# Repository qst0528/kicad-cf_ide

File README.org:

* CompactFlash cards and DMA/UDMA support in True IDE (tm) mode
http://support.fccps.cz/download/adv/frr/cf.html

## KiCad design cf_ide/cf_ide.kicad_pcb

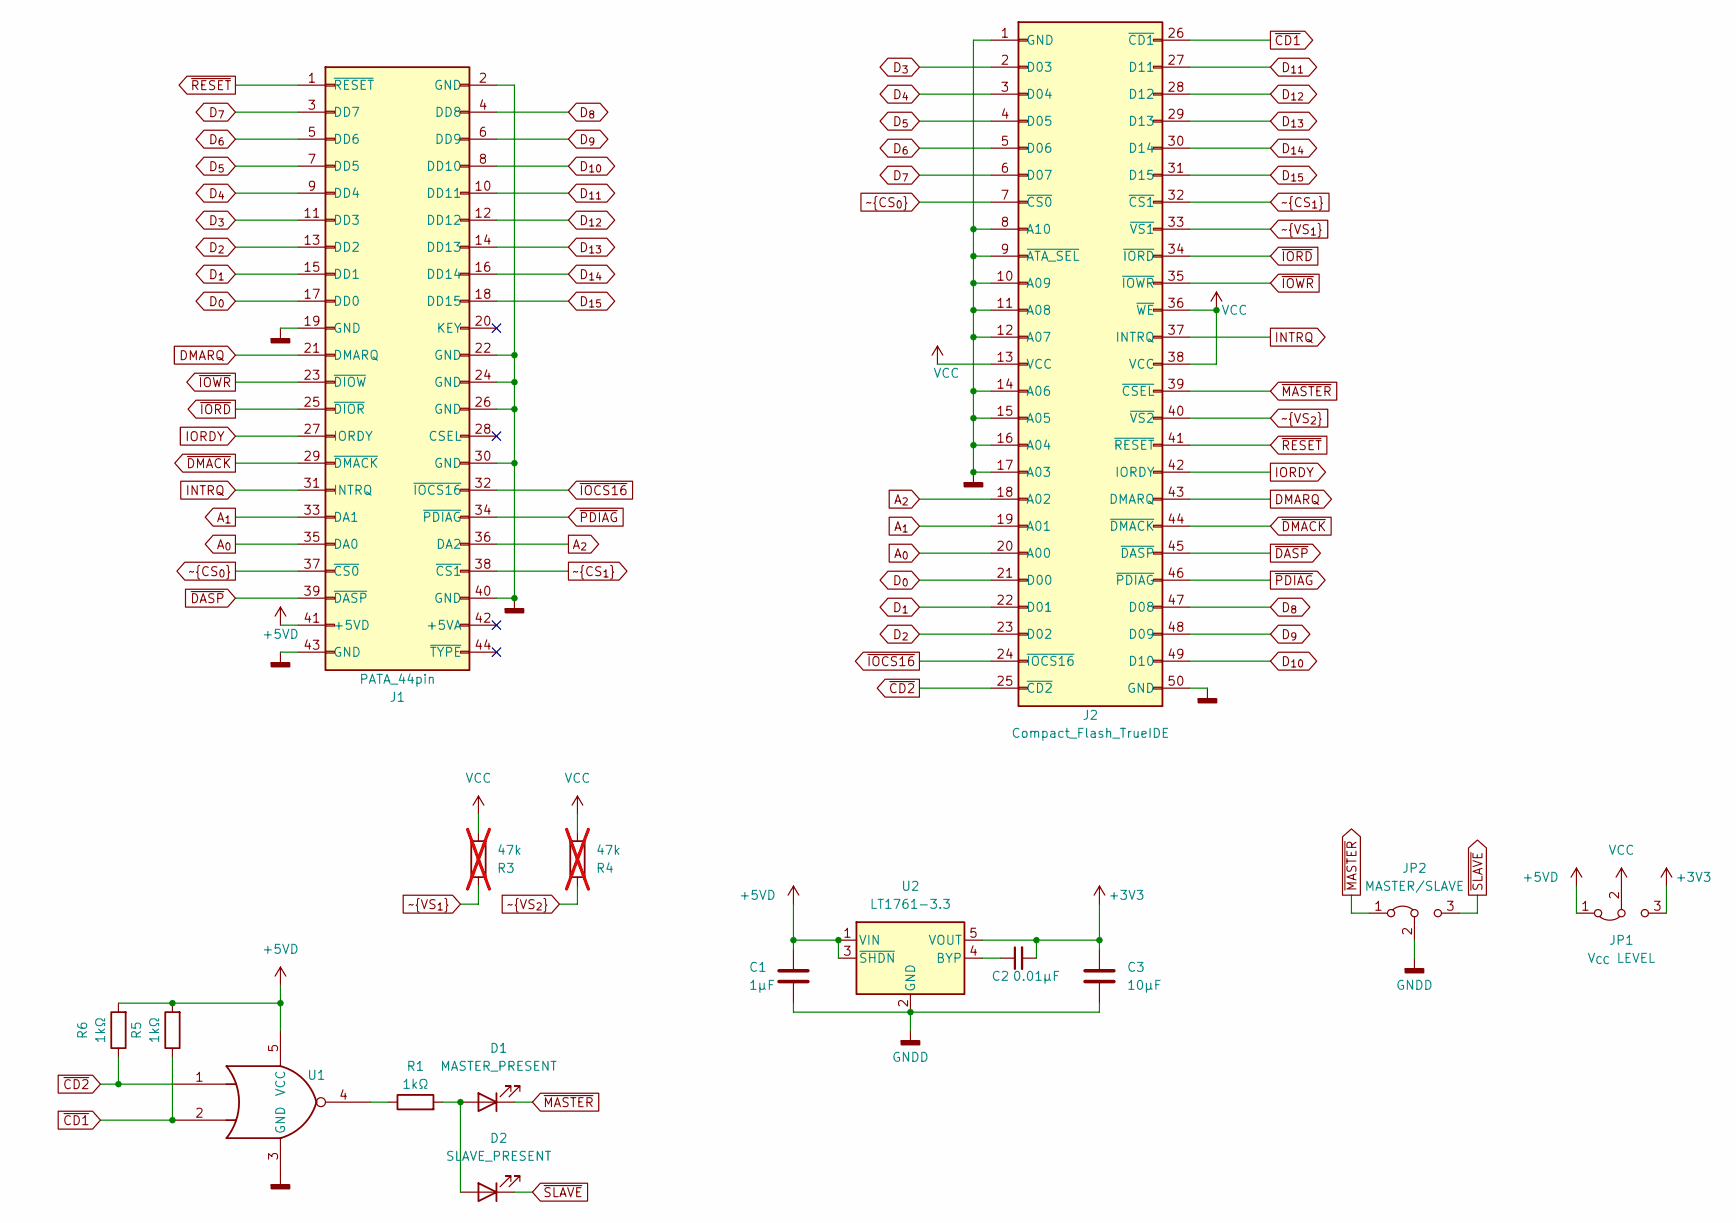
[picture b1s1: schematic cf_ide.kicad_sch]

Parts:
C1: 1μF; C_0805_2012Metric_Pad1.18x1.45mm_HandSolder
C2: 0.01μF; C_1206_3216Metric_Pad1.33x1.80mm_HandSolder
C3: 10μF; C_1210_3225Metric_Pad1.33x2.70mm_HandSolder
D1: MASTER_PRESENT; LED_0603_1608Metric_Pad1.05x0.95mm_HandSolder
D2: SLAVE_PRESENT; LED_0603_1608Metric_Pad1.05x0.95mm_HandSolder
J1: PATA_44pin; PinSocket_2x22_P2.00mm_Vertical
J2: Compact_Flash_TrueIDE; CF-Card_3M_N7E50-A516xx-30
JP1: V_{CC} LEVEL; PinHeader_1x03_P2.54mm_Vertical
JP2: MASTER/SLAVE; PinHeader_1x03_P2.54mm_Vertical
R1, R5, R6: 1kΩ; R_0603_1608Metric_Pad0.98x0.95mm_HandSolder
R3, R4: 47k; R_0603_1608Metric_Pad0.98x0.95mm_HandSolder; not fitted
U1: 74AHC1G02; SOT-353_SC-70-5_Handsoldering
U2: LT1761-3.3; TSOT-23-5

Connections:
+3V3: C2.2, C3.1, JP1.3 (B), U2.5 (VOUT)
+5VD: C1.1, J1.41 (+5VD), JP1.1 (A), R5.2, R6.2, U1.5 (VCC), U2.1 (VIN), U2.3 (~SHDN)
A_{0}: J1.35 (DA0), J2.20 (A00)
A_{1}: J1.33 (DA1), J2.19 (A01)
A_{2}: J1.36 (DA2), J2.18 (A02)
DMARQ: J1.21 (DMARQ), J2.43 (DMARQ)
D_{0}: J1.17 (DD0), J2.21 (D00)
D_{1}: J1.15 (DD1), J2.22 (D01)
D_{2}: J1.13 (DD2), J2.23 (D02)
D_{3}: J1.11 (DD3), J2.2 (D03)
D_{4}: J1.9 (DD4), J2.3 (D04)
D_{5}: J1.7 (DD5), J2.4 (D05)
D_{6}: J1.5 (DD6), J2.5 (D06)
D_{7}: J1.3 (DD7), J2.6 (D07)
D_{8}: J1.4 (DD8), J2.47 (D08)
D_{9}: J1.6 (DD9), J2.48 (D09)
D_{10}: J1.8 (DD10), J2.49 (D10)
D_{11}: J1.10 (DD11), J2.27 (D11)
D_{12}: J1.12 (DD12), J2.28 (D12)
D_{13}: J1.14 (DD13), J2.29 (D13)
D_{14}: J1.16 (DD14), J2.30 (D14)
D_{15}: J1.18 (DD15), J2.31 (D15)
GNDD: C1.2, C3.2, J1.2 (GND), J1.19 (GND), J1.22 (GND), J1.24 (GND), J1.26 (GND), J1.30 (GND), J1.40 (GND), J1.43 (GND), J2.1 (GND), J2.8 (A10), J2.9 (~ATA_SEL), J2.10 (A09), J2.11 (A08), J2.12 (A07), J2.14 (A06), J2.15 (A05), J2.16 (A04), J2.17 (A03), J2.50 (GND), JP2.2 (C), U1.3 (GND), U2.2 (GND)
INTRQ: J1.31 (INTRQ), J2.37 (INTRQ)
IORDY: J1.27 (IORDY), J2.42 (IORDY)
unnamed: D1.2 (A), D2.2 (A), R1.2
unnamed: R1.1, U1.4
unnamed: C2.1, U2.4 (BYP)
VCC: J2.13 (VCC), J2.36 (~WE), J2.38 (VCC), JP1.2 (C), R3.2, R4.2
~CD1: J2.26 (~CD1), R5.1, U1.2
~CD2: J2.25 (~CD2), R6.1, U1.1
~CS_{0}: J1.37 (~CS0), J2.7 (~CS0)
~CS_{1}: J1.38 (~CS1), J2.32 (~CS1)
~DASP: J1.39 (~DASP), J2.45 (~DASP)
~DMACK: J1.29 (~DMACK), J2.44 (~DMACK)
~IOCS16: J1.32 (~IOCS16), J2.24 (~IOCS16)
~IORD: J1.25 (~DIOR), J2.34 (~IORD)
~IOWR: J1.23 (~DIOW), J2.35 (~IOWR)
~MASTER: D1.1 (K), J2.39 (~CSEL), JP2.1 (A)
~PDIAG: J1.34 (~PDIAG), J2.46 (~PDIAG)
~RESET: J1.1 (~RESET), J2.41 (~RESET)
~SLAVE: D2.1 (K), JP2.3 (B)
~VS_{1}: J2.33 (~VS1), R3.1
~VS_{2}: J2.40 (~VS2), R4.1

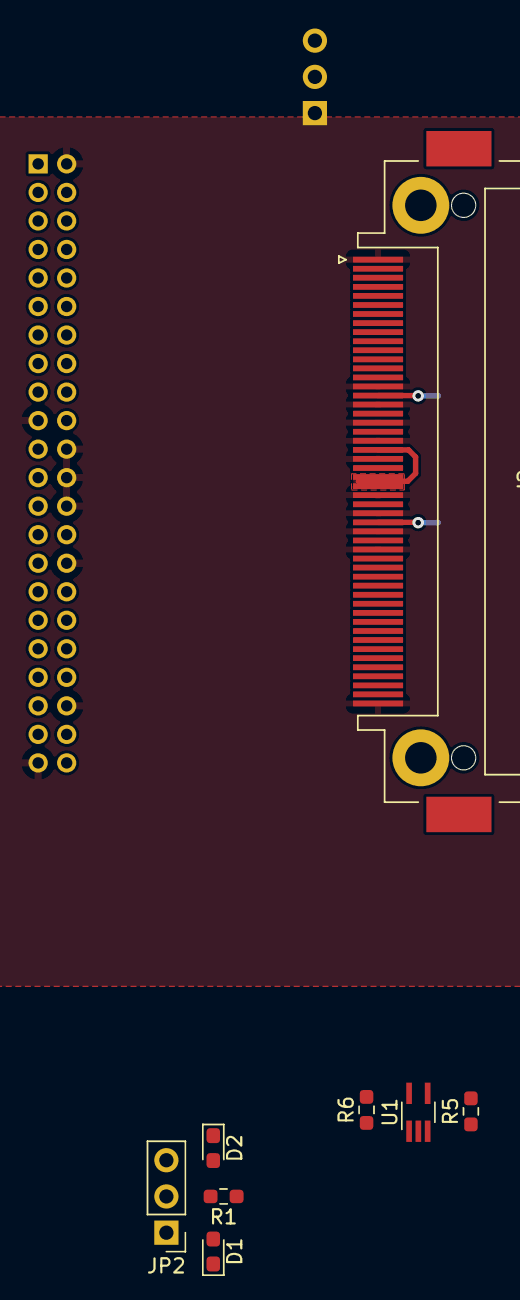
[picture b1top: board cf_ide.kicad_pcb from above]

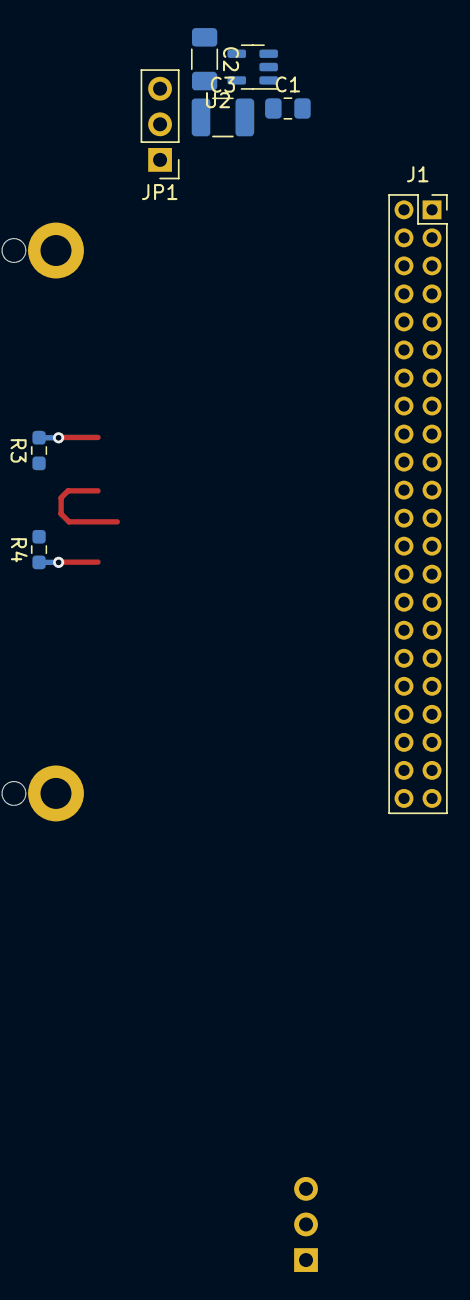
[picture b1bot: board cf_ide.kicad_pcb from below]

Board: 2 copper layers, 16 parts (8 on the bottom side), 44 nets.

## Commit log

2024-04-16 Initialize repo
2024-04-16 Add LICENSE
2024-04-16 Remove unneeded pull up/downs
2024-04-18 Start PCB design
